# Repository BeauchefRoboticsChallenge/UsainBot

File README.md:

# UsainBot
[![CC BY NC SA 4.0][cc-by-nc-sa-shield]][cc-by-nc-sa]

UsainBot es un robot velocista del tipo seguidor de líneas cuyo objetivo es servir de referencia y plataforma para apoyar en la formación de los competidores. Está desarrollado en base a las tecnologías disponibles en un FabLab (impresión 3D, corte de PCBs, Arduino) y comprende las componentes más básicas para funcionar de acuerdo a las reglas de la competencia.

Un velocista seguidor de línea es un robot con ruedas que tiene la capacidad de distinguir franjas en una superficie de alto contraste (blanco y negro) y seguir su trayectoria de forma autónoma con la finalidad de completar un circuito lo más rápido posible.

# Diseño

## Antecedentes

Las funciones principales requeridas por el robot son:

- Reconocer franjas
- Movimiento
- Energía
- Procesamiento y control

Para esto requiere una construcción óptima en cuanto al tamaño/peso y las prestaciones de sus componentes que cumplirán estas funcionalidades, las cuales pueden ser desempeñadas por diferentes tipos y arreglos de sensores, motores, baterías, etc. Otras funciones secundarias corresponden a la interacción con el usuario (encender/apagar, activar, indicar acciones), así como cualquier otra que se desee agregar (como comunicación inalámbrica para el debugging).

En el contexto de la competencia, existirán marcadores a los costados del circuito que indicarán hitos como curvas, cruces y fin. También se fija el tamaño máximo como 25x25x20 centímetros (largo, ancho y alto) y que las ruedas no pueden contener elementos adherentes que dañen la pista.

(imagen de los hitos)

## Diseño original

UsainBot se diseñó considerando este set mínimo de subsistemas, las tecnologías disponibles en el Fablab U de Chile, la disponibilidad de componentes comerciales en el país (Chile) y otros diseños populares de robots velocistas. Los dibujos del sistema se realizaron en AutodeskFusion 360 y se llegó al siguiente diseño:

(vistas del usainbot)

### Sensores

UsainBot cuenta con un arreglo de sensores infrarrojos modelo asdasdasdsad en el frente. Esta disposición permite detectar con cierto nivel de resolución la desviación del eje central del robot respecto a la franja del circuito y tener un mejor control:

(esquema)

También posee dos sensores simples del mismo tipo (modelo sadads) en cada lado para la detección de franjas.

(imagen con zoom)

### Actuación

El robot posee una configuración diferencial, dos ruedas controladas por motores DC idénticos modelo asdasdsad, de x rpm nominales y v Volts.

La llanta de la rueda, impresa en 3D, posee una muesca donde se inserta el eje del motor (que tiene una muesca opuesta) a presión, mientras que el neumático es de silicona.

Los motores se apernan al chasis mediante soportes impresos en 3D.

Considerando la corriente que requieren estos motores elegimos utilizar como driver el puente H sadasdasdasd.

### Controlador

Decidimos utilizar un Arduino Nano por varias razones: Soporte de software, tamaño, lógica de 5V (compatible con el resto de componentes), disponibilidad, precio, facilidad de uso (cuenta con pines y puerto USB), entre otras.

### Batería

Considerando el voltaje necesario para el controlador y los motores, los cuales además suelen requerir altos niveles de corriente súbitamente es que elegimos utilizar una batería LiPo de 7.4 V modelo asdsdasad. Con tal capacidad permitirá realizar pruebas un par de horas antes de volver a cargarla sin conllevar mucho peso sobre el sistema.

### Chasis

Con el objetivo de minimizar el peso y tamaño se diseña una PCB con doble propósito: ubicar los componentes en el mínimo espacio posible y como chasis del robot, considerando que la placa de sadklsdajlkasdjlk tiene rigidez suficiente.

(imagen de la PCB)

La PCB tiene conectores para intercambiar fácilmente los componentes en caso de que sufran algún desperfecto, así como orificios para el montaje de los motores.

### Otros

Como tercer punto de apoyo se utiliza la parte cabeza de un LED redondo.

Utilizamos un buzzer standard de 5V para que el robot informe mediante alertas sonoras el estado en el que se encuentra.

Incluimos un switch para energizar los sistemas desde la batería y un pulsador para iniciar la rutina de carrera.

# Lista de partes y materiales

## Partes comerciales

Item                     | Cantidad
 ---------------------------   | --------------
Motor DC con reducción 6V x rpm | 2
Driver asdasd | 1
Sensor QTR-8A | 1
Sensor QTR-1A | 2
Arduino Nano | 1
Lipo 7.4V | 1
Pulsador | 1
Switch | 1
LED | 1
Buzzer | 1

Otros elementos necesarios para el desarrollo del robot pero no que son parte del mismo corresponden a: cargador de LiPo, alarma de carga de batería.

## Partes manufacturadas

Item                     | Cantidad
 ---------------------------   | ------------
Llantas | 2
Neumáticos | 2
Chasis PCB | 1

## Materiales

- pines, conectores,
- placa fr-4
- silicona epóxica 20-50 Shore A
- pernos m3x8 (4)
- tuerca m3 (4)

# Manufactura

## Componentes

### Llantas y neumáticos

Dado que tenemos acceso a una impresora de tipo SLA (Form2), decidimos fabricar las llantas con resina tenaz (Tough Resin) para soportar posibles golpes y el ajuste a presión sobre el eje, y moldes para los neumáticos con resina estándar translúcida (Clear Resin), pues de esta forma es fácil desprender la pieza moldeada del molde mismo y además permite observar la presencia de burbujas durante el procseo de curado.

El neumático se fabrica directamente sobre la llanta, como se muestra en el diagrama:

Para el proceso es necesario mezclar la silicona en partes iguales, revolver y degasificar rapidamente antes de que la silicona empiece a solidificarse.

### Anclajes de motor

Estos anclajes afirman el motor utilizando pernos M3x8 y tuercas M3, son impresos en FDM con PLA.

### PCB

Para la manufactura de la PCB contamos con una máquina LPKF modelo sadasdsda. Las herramientas que utilizamos para el corte son:

- sdaasd
- asdsd
- sadsdasadsda

Antes de empezar a soldar los componentes es importante probar la integridad de las pistas midiendo la conductividad con un multímetro, para evitar corto circuitos y circuitos abiertos.

Luego soldamos los pines, buzzer, pulsador, switch y LED de acuerdo al esquema.

## Ensamble

1.- Montar las ruedas en cada motor
2.- Montar los motores con sus anclajes sobre la PCB.
3.- Conectar Arduino Nano
4.- Conectar sensores laterales
5.- Conectar arreglo de sensores frontal.
6.- Conectar driver.
7.- Montar batería con un elástico y conectar.

# Software

## Pista de pruebas

Para hacer pruebas de funcionamiento resulta muy útil tener una pequeña pista de pruebas, esta la fabricamos con un trozo de melamina delgado de color negro y cinta aislante de x mm de ancho de color blanco.

(imagen de la pista)

## Pruebas de subsistemas

Una vez que el sistema está ensamblado, los componentes deben ser probados separadamente antes de hacer la integración final. Para esto generamos códigos sencillos para ejecutar en el robot y observar tanto su funcionamiento como la información que entrega el Arduino a través del monitor serial.

- Prueba de motores.
- Prueba de sensores principal.
- Prueba de sensores laterales.

(links a los codigos)

## Integración

## Calibración del PID

El funcionamiento óptimo del robot implica maximizar la velocidad manteniendo el robot moviéndose dentro de la franja y colineal con esta. Para esto es necesario encontrar una configuración óptima de los parámetros del PID.

### Calibración "manual"

De acuerdo al comportamiento observado en las pruebas, se pueden hacer las siguientes modificaciones:

## Licencia
[![CC BY NC SA 4.0][cc-by-nc-sa-image]][cc-by-nc-sa]

Este trabajo esta publicado bajo la licencia [Creative Commons Attribution-NonCommercial-ShareAlike 4.0 International
License][cc-by-nc-sa].

Si deseas utilizar nuestro robot en tus proyectos o si te interesa vender las placas, contáctanos y conversemos :)

[cc-by-nc-sa]: https://creativecommons.org/licenses/by-nc-sa/4.0/
[cc-by-nc-sa-image]: https://i.creativecommons.org/l/by-nc-sa/4.0/88x31.png
[cc-by-nc-sa-shield]: https://img.shields.io/badge/License-CC%20BY%20NC%20SA%204.0-lightgrey.svg

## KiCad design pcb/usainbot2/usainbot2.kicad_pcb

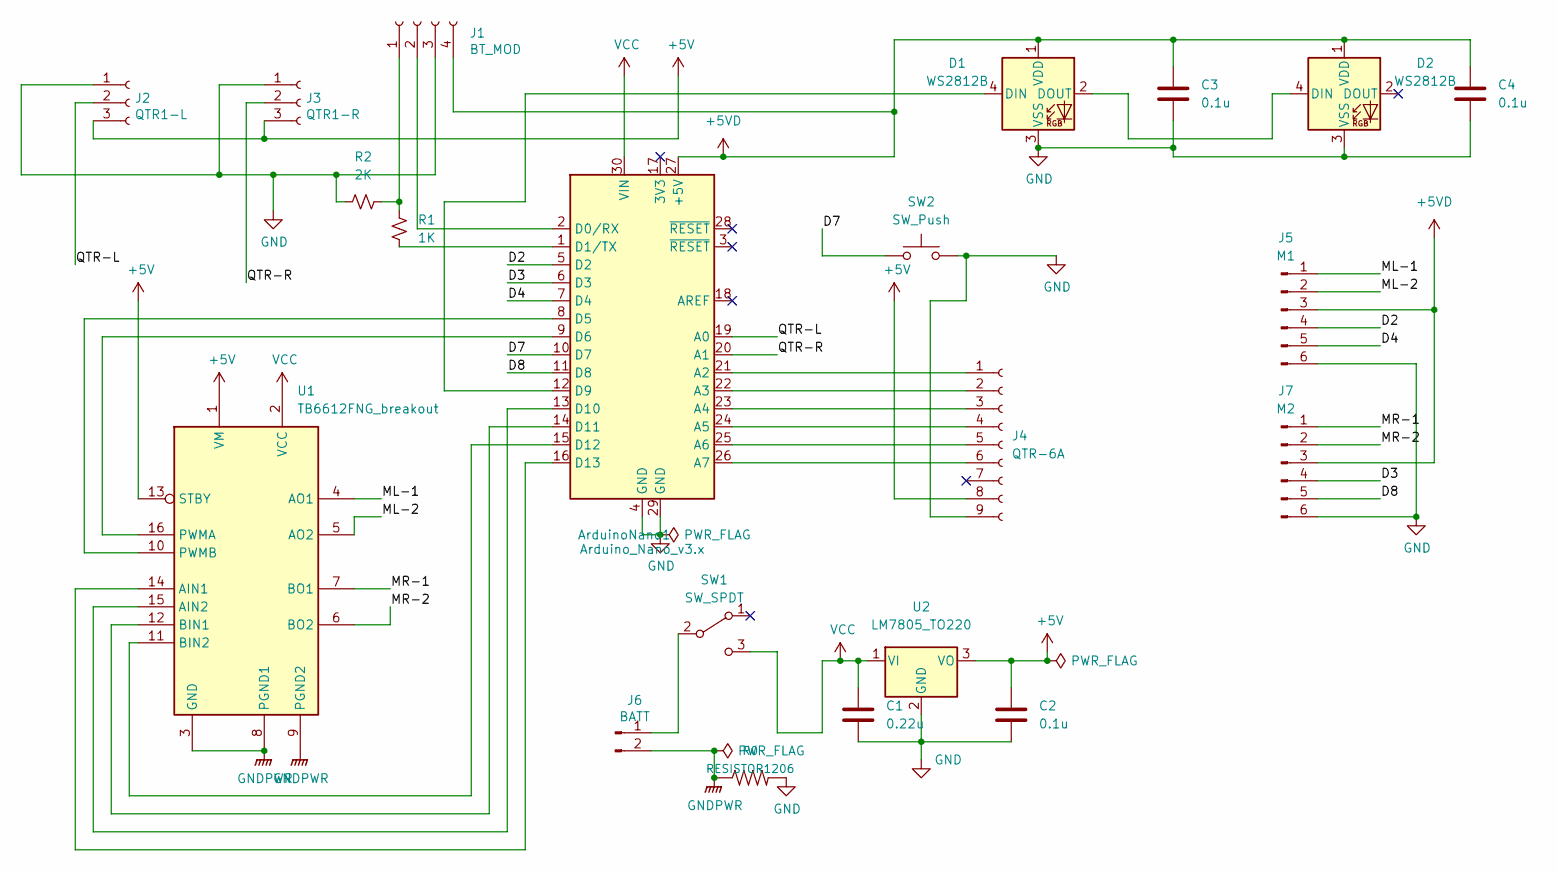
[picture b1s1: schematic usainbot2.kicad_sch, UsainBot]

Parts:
ArduinoNano1: Arduino_Nano_v3.x; Arduino_Nano
C1: 0.22u; C_0805_2012Metric_Pad1.18x1.45mm_HandSolder
C2, C3, C4: 0.1u; C_0805_2012Metric_Pad1.18x1.45mm_HandSolder
D1, D2: WS2812B; LED_WS2812B_PLCC4_5.0x5.0mm_P3.2mm
J1: BT_MOD; PinHeader_1x04_P2.54mm_Vertical
J2: QTR1-L; PinHeader_1x03_P2.54mm_Horizontal
J3: QTR1-R; PinHeader_1x03_P2.54mm_Horizontal
J4: QTR-6A; PinHeader_1x09_P2.54mm_Horizontal
J5: M1; Molex_KK-254_AE-6410-06A_1x06_P2.54mm_Vertical
J6: BATT; Molex_KK-254_AE-6410-02A_1x02_P2.54mm_Vertical
J7: M2; Molex_KK-254_AE-6410-06A_1x06_P2.54mm_Vertical
R0: RESISTOR1206; R_1206_3216Metric
R1: 1K; R_1206_3216Metric_Pad1.30x1.75mm_HandSolder
R2: 2K; R_1206_3216Metric_Pad1.30x1.75mm_HandSolder
SW1: SW_SPDT; SPST slide switch
SW2: SW_Push; SW_Push_1P1T_NO_Vertical_Wuerth_434133025816
U1: TB6612FNG_breakout; TB6612FNG Breakout
U2: LM7805_TO220; TO-220-3_Vertical

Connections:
+5V: C2.1, J2.3, J3.3, J4.8, U1.1 (VM), U1.13 (STBY), U2.3 (VO)
+5VD: ArduinoNano1.27 (+5V), C3.1, C4.1, D1.1 (VDD), D2.1 (VDD), J1.4, J5.3, J7.3
/D2: ArduinoNano1.5 (D2), J5.4
/D3: ArduinoNano1.6 (D3), J7.4
/D4: ArduinoNano1.7 (D4), J5.5
/D7: ArduinoNano1.10 (D7), SW2.1
/D8: ArduinoNano1.11 (D8), J7.5
/ML-1: J5.1, U1.4 (AO1)
/ML-2: J5.2, U1.5 (AO2)
/MR-1: J7.1, U1.7 (BO1)
/MR-2: J7.2, U1.6 (BO2)
/QTR-L: ArduinoNano1.19 (A0), J2.2
/QTR-R: ArduinoNano1.20 (A1), J3.2
GND: ArduinoNano1.4 (GND), ArduinoNano1.29 (GND), C1.2, C2.2, C3.2, C4.2, D1.3 (VSS), D2.3 (VSS), J1.3, J2.1, J3.1, J4.9, J5.6, J7.6, R0.2, R2.2, SW2.2, U2.2 (GND)
GNDPWR: J6.2, R0.1, U1.3 (GND), U1.8 (PGND1), U1.9 (PGND2)
unnamed: ArduinoNano1.1 (D1/TX), R1.2
unnamed: ArduinoNano1.2 (D0/RX), J1.2
unnamed: ArduinoNano1.8 (D5), U1.10 (PWMB)
unnamed: ArduinoNano1.9 (D6), U1.16 (PWMA)
unnamed: ArduinoNano1.12 (D9), D1.4 (DIN)
unnamed: ArduinoNano1.13 (D10), U1.15 (AIN2)
unnamed: ArduinoNano1.14 (D11), U1.12 (BIN1)
unnamed: ArduinoNano1.15 (D12), U1.11 (BIN2)
unnamed: ArduinoNano1.16 (D13), U1.14 (AIN1)
unnamed: ArduinoNano1.21 (A2), J4.1
unnamed: ArduinoNano1.22 (A3), J4.2
unnamed: ArduinoNano1.23 (A4), J4.3
unnamed: ArduinoNano1.24 (A5), J4.4
unnamed: ArduinoNano1.25 (A6), J4.5
unnamed: ArduinoNano1.26 (A7), J4.6
unnamed: D1.2 (DOUT), D2.4 (DIN)
unnamed: J1.1, R1.1, R2.1
unnamed: J6.1, SW1.2 (B)
VCC: ArduinoNano1.30 (VIN), C1.1, SW1.3 (C), U1.2 (VCC), U2.1 (VI)

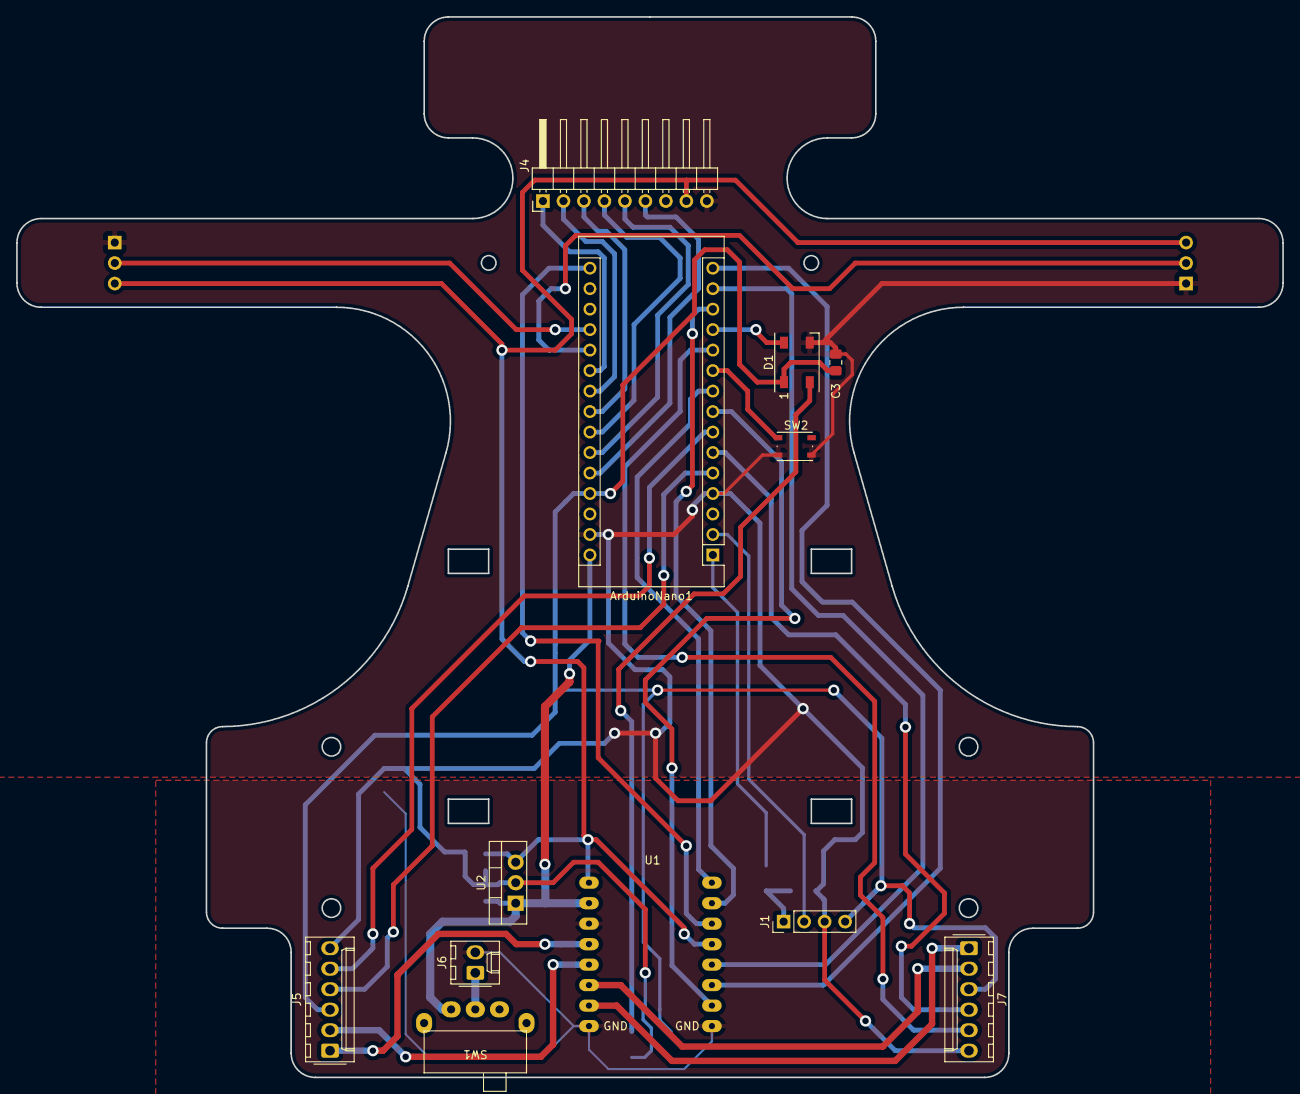
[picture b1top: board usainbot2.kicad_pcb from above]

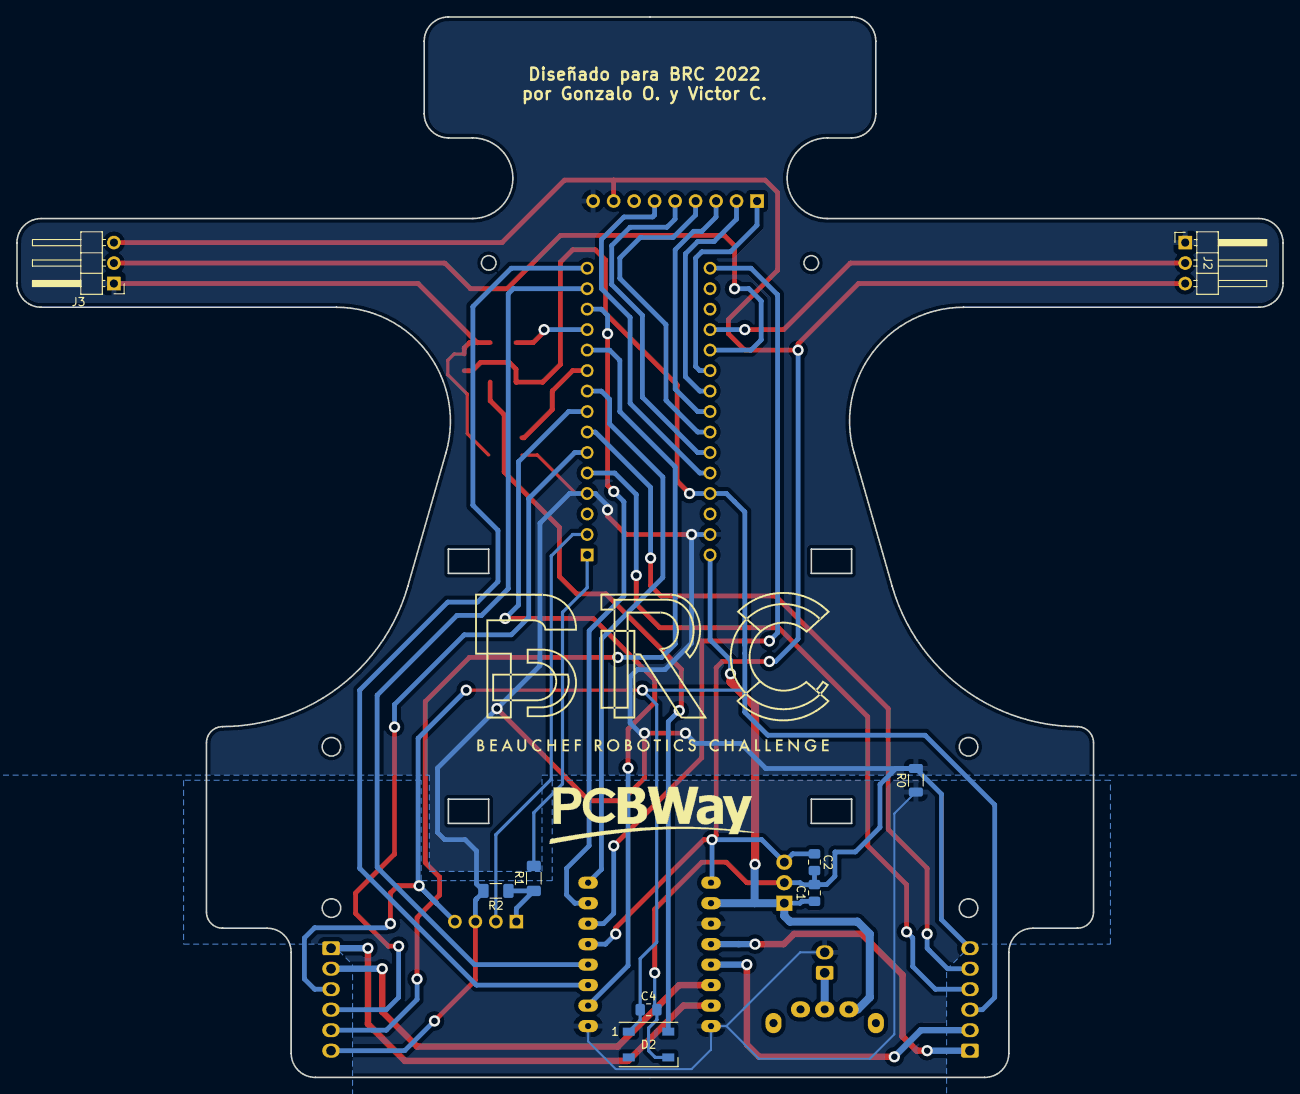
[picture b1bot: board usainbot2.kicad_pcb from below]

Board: 2 copper layers, 157.0 x 131.5 mm, 21 parts (9 on the bottom side), 34 nets.

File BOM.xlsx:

Id | Designator | Package | Quantity | Designation | Supplier and ref
1 | U1 | TB6612FNG Breakout | 1 | TB6612FNG_breakout
 |  |  | 2 | pin socket 8x1
2 | J1 | PinSocket_1x04_P2.54mm_Vertical | 1 | BT_MOD
 |  |  | 1 | pin socket 4x1
3 | ArduinoNano1 | Arduino_Nano | 1 | Arduino_Nano_v3.x
 |  |  | 2 | pin socket 15x1
4 | C3,C2,C4 | C_0805_2012Metric_Pad1.18x1.45mm_HandSolder | 3 | 0.1u
5 | J5 | Molex_KK-254_AE-6410-06A_1x06_P2.54mm_Vertical | 1 | M1
6 | D1,D2 | LED_WS2812B_PLCC4_5.0x5.0mm_P3.2mm | 2 | WS2812B
7 | SW1 | SPST slide switch | 1 | SW_SPDT
8 | SW2 | SW_Push_1P1T_NO_Vertical_Wuerth_434133025816 | 1 | SW_Push
9 | U2 | TO-220-3_Vertical | 1 | LM7805_TO220
 |  |  | 1 | pin socket 3x1
10 | J7 | Molex_KK-254_AE-6410-06A_1x06_P2.54mm_Vertical | 1 | M2
11 | J6 | Molex_KK-254_AE-6410-02A_1x02_P2.54mm_Vertical | 1 | BATT
12 | J4 | PinHeader_1x09_P2.54mm_Horizontal | 1 | QTR-6A
13 | J3 | PinHeader_1x03_P2.54mm_Vertical | 1 | QTR1-R
14 | R0 | R_1206_3216Metric | 1 | RESISTOR1206
15 | J2 | PinHeader_1x03_P2.54mm_Vertical | 1 | QTR1-L
16 | R1 | R_1206_3216Metric_Pad1.30x1.75mm_HandSolder | 1 | 1K
17 | R2 | R_1206_3216Metric_Pad1.30x1.75mm_HandSolder | 1 | 2K
18 | C1 | C_0805_2012Metric_Pad1.18x1.45mm_HandSolder | 1 | 0.22u

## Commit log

2020-09-01 resumen and some shiets
2020-09-01 más texto
2022-03-31 add board and gitignore
2022-04-13 update pcb, falta rutear
2022-04-19 sv with layers for milling
2022-04-19 last pcb update
2022-05-20 update firmware
2022-05-20 robot racer v2.1 kicad
2022-05-20 add power switch footprint
2022-05-20 add outline final dxf
2022-05-23 add led and add top pwrgnd isolation copper
2022-05-30 add logos in silkscreen
2022-05-30 add gitignore
2022-06-06 updated pcb silkscreen and v3 firmware
2022-06-07 add TB6612FNG documentation and update pcb
2022-06-07 add license and modified readme
2022-08-19 cambios al firmware del v3
2022-08-19 nuevo archivo de definiciones de los pines del robot
2022-10-05 racerv3
2022-10-05 todo
2022-12-14 de agrega standby
2023-05-16 integra standby con corrección de mapeo
2023-05-16 add vel control sketch

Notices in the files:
pcb/usainbot2/usainbot2.kicad_pcb:
creativecommons.org/licenses/by/4.0
License: CC BY 4.0
